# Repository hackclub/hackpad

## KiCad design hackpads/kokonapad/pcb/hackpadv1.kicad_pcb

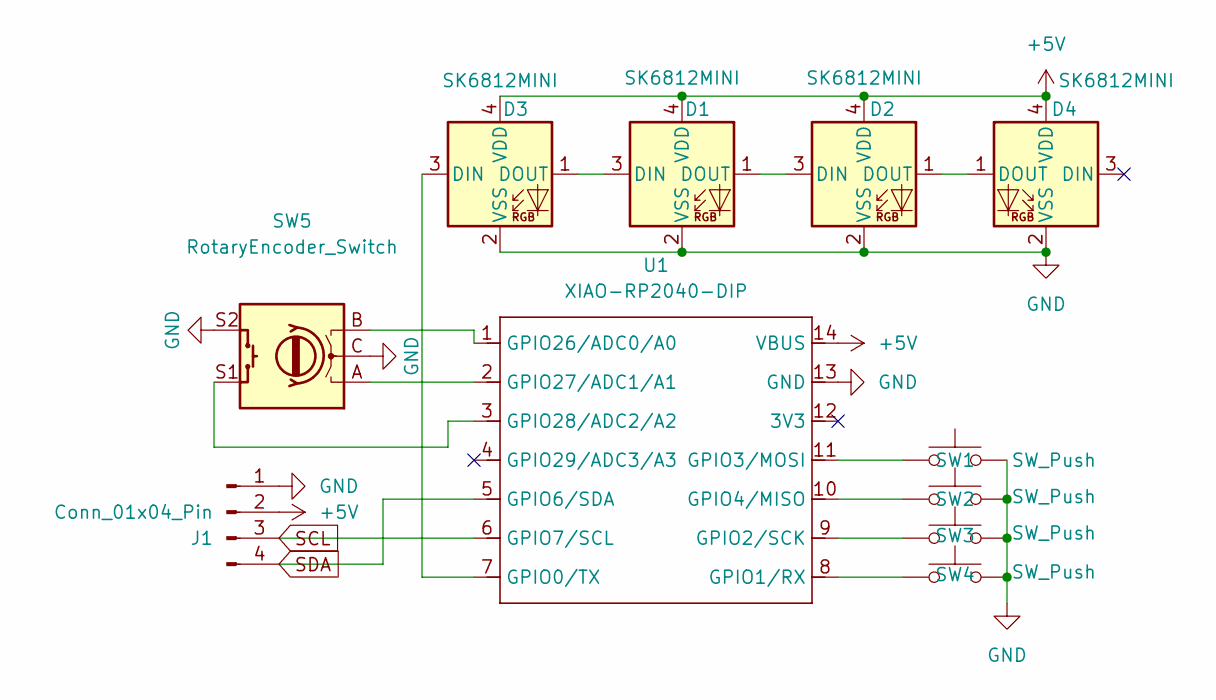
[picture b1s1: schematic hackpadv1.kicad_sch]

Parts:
D1, D2, D3, D4: SK6812MINI; LED_SK6812MINI_PLCC4_3.5x3.5mm_P1.75mm
J1: Conn_01x04_Pin; SSD1306-0.91-OLED-4pin-128x32
SW1, SW2, SW3, SW4: SW_Push; SW_Cherry_MX_1.00u_PCB
SW5: RotaryEncoder_Switch; RotaryEncoder_Alps_EC11E-Switch_Vertical_H20mm_CircularMoun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
U1: XIAO-RP2040-DIP

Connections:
+5V: D1.4 (VDD), D2.4 (VDD), D3.4 (VDD), D4.4 (VDD), J1.2, U1.14 (VBUS)
GND: D1.2 (VSS), D2.2 (VSS), D3.2 (VSS), D4.2 (VSS), J1.1, SW1.2, SW2.2, SW3.2, SW4.2, SW5.C, SW5.S2, U1.13 (GND)
unnamed: D1.3 (DIN), D3.1 (DOUT)
unnamed: D1.1 (DOUT), D2.3 (DIN)
unnamed: D2.1 (DOUT), D4.1 (DOUT)
unnamed: D3.3 (DIN), U1.7 (GPIO0/TX)
unnamed: SW4.1, U1.8 (GPIO1/RX)
unnamed: SW3.1, U1.9 (GPIO2/SCK)
unnamed: SW1.1, U1.11 (GPIO3/MOSI)
unnamed: SW2.1, U1.10 (GPIO4/MISO)
unnamed: SW5.B, U1.1 (GPIO26/ADC0/A0)
unnamed: SW5.A, U1.2 (GPIO27/ADC1/A1)
unnamed: SW5.S1, U1.3 (GPIO28/ADC2/A2)
SCL: J1.3, U1.6 (GPIO7/SCL)
SDA: J1.4, U1.5 (GPIO6/SDA)

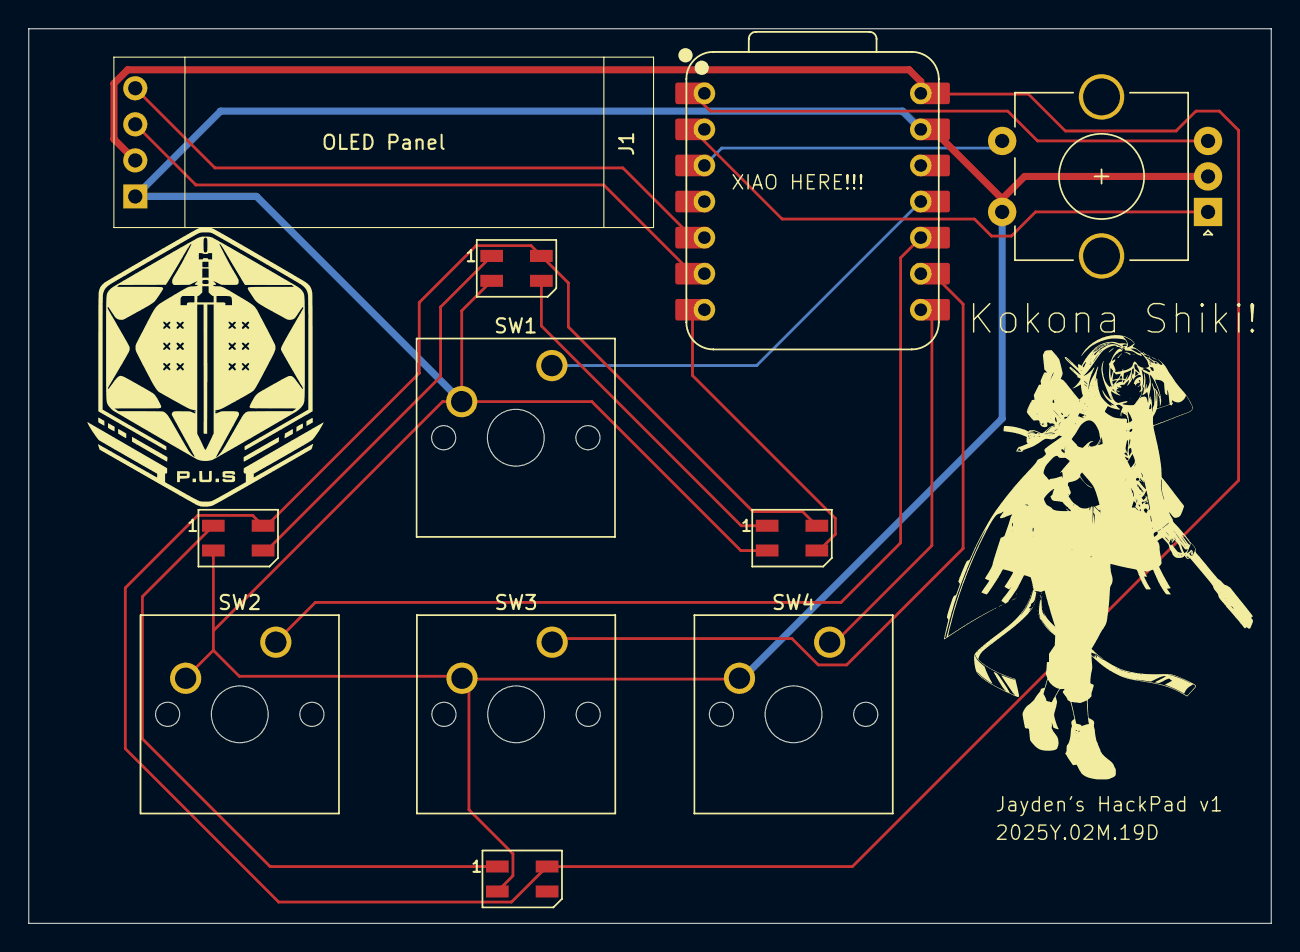
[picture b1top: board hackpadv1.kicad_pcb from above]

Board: 2 copper layers, 87.5 x 63.0 mm, 11 parts (0 on the bottom side), 15 nets.

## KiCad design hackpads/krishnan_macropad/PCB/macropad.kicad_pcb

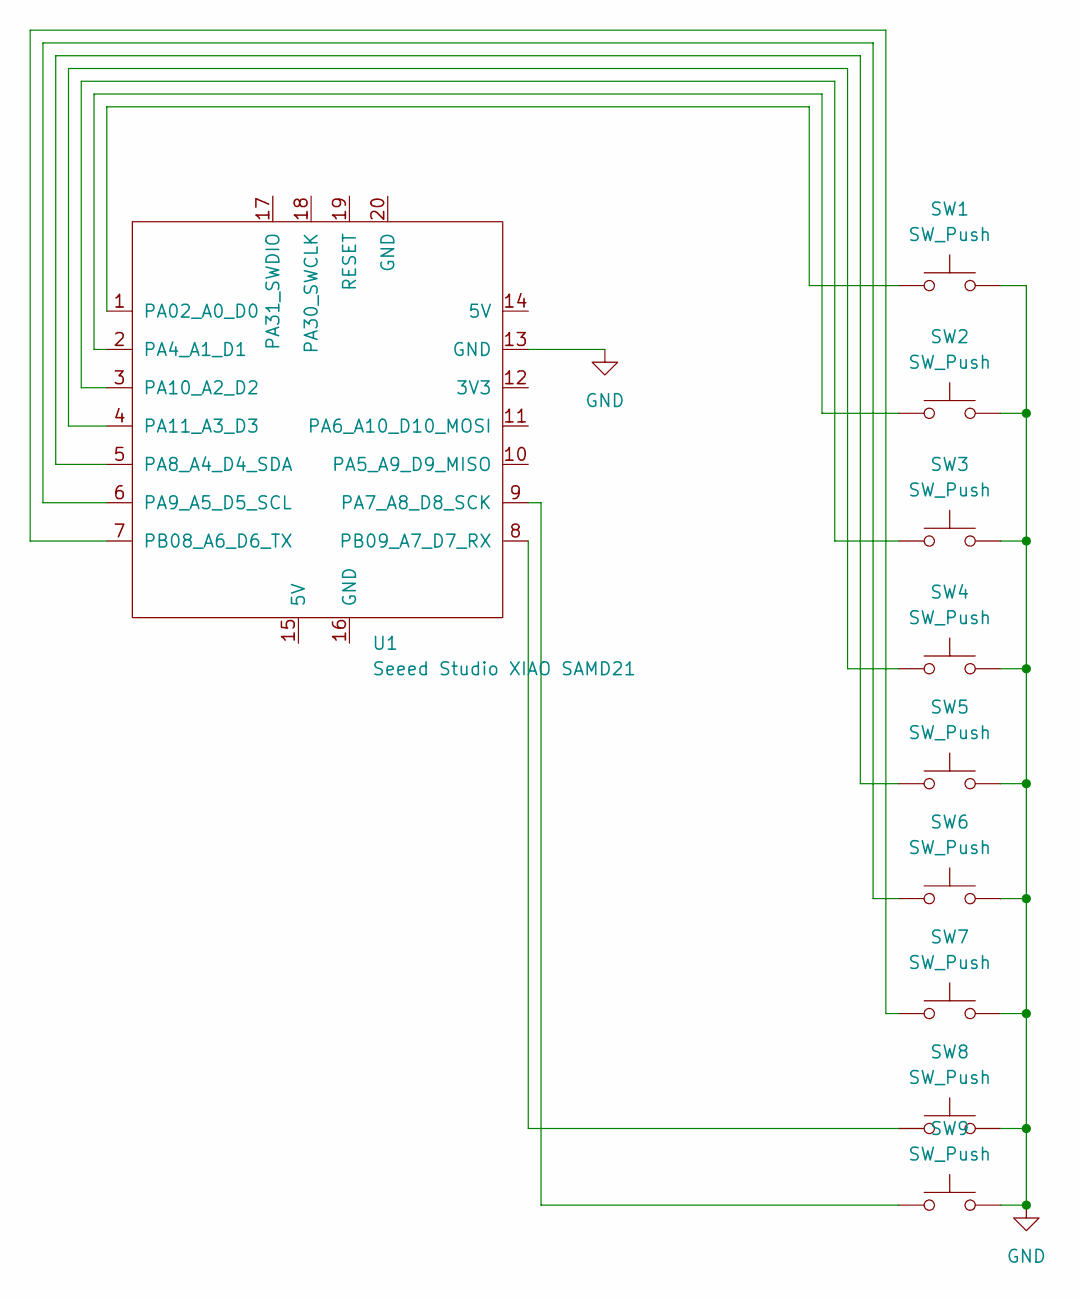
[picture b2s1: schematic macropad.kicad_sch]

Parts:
SW1, SW2, SW3, SW4, SW5, SW6, SW7, SW8, SW9: SW_Push; SW_Cherry_MX_1.00u_PCB
U1: Seeed Studio XIAO SAMD21; XIAO-RP2040-DIP

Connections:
GND: SW1.2, SW2.2, SW3.2, SW4.2, SW5.2, SW6.2, SW7.2, SW8.2, SW9.2, U1.13 (GND)
unnamed: SW1.1, U1.1 (PA02_A0_D0)
unnamed: SW2.1, U1.2 (PA4_A1_D1)
unnamed: SW9.1, U1.9 (PA7_A8_D8_SCK)
unnamed: SW5.1, U1.5 (PA8_A4_D4_SDA)
unnamed: SW6.1, U1.6 (PA9_A5_D5_SCL)
unnamed: SW3.1, U1.3 (PA10_A2_D2)
unnamed: SW4.1, U1.4 (PA11_A3_D3)
unnamed: SW7.1, U1.7 (PB08_A6_D6_TX)
unnamed: SW8.1, U1.8 (PB09_A7_D7_RX)

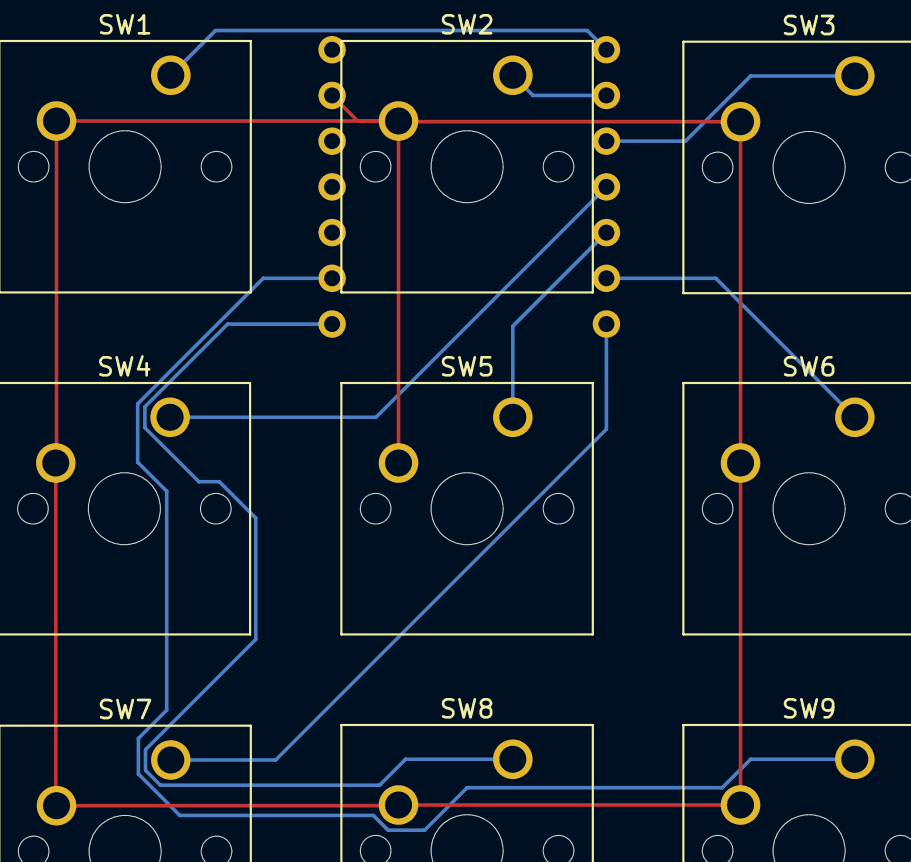
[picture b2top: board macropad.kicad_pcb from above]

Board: 2 copper layers, 10 parts (1 on the bottom side), 10 nets.

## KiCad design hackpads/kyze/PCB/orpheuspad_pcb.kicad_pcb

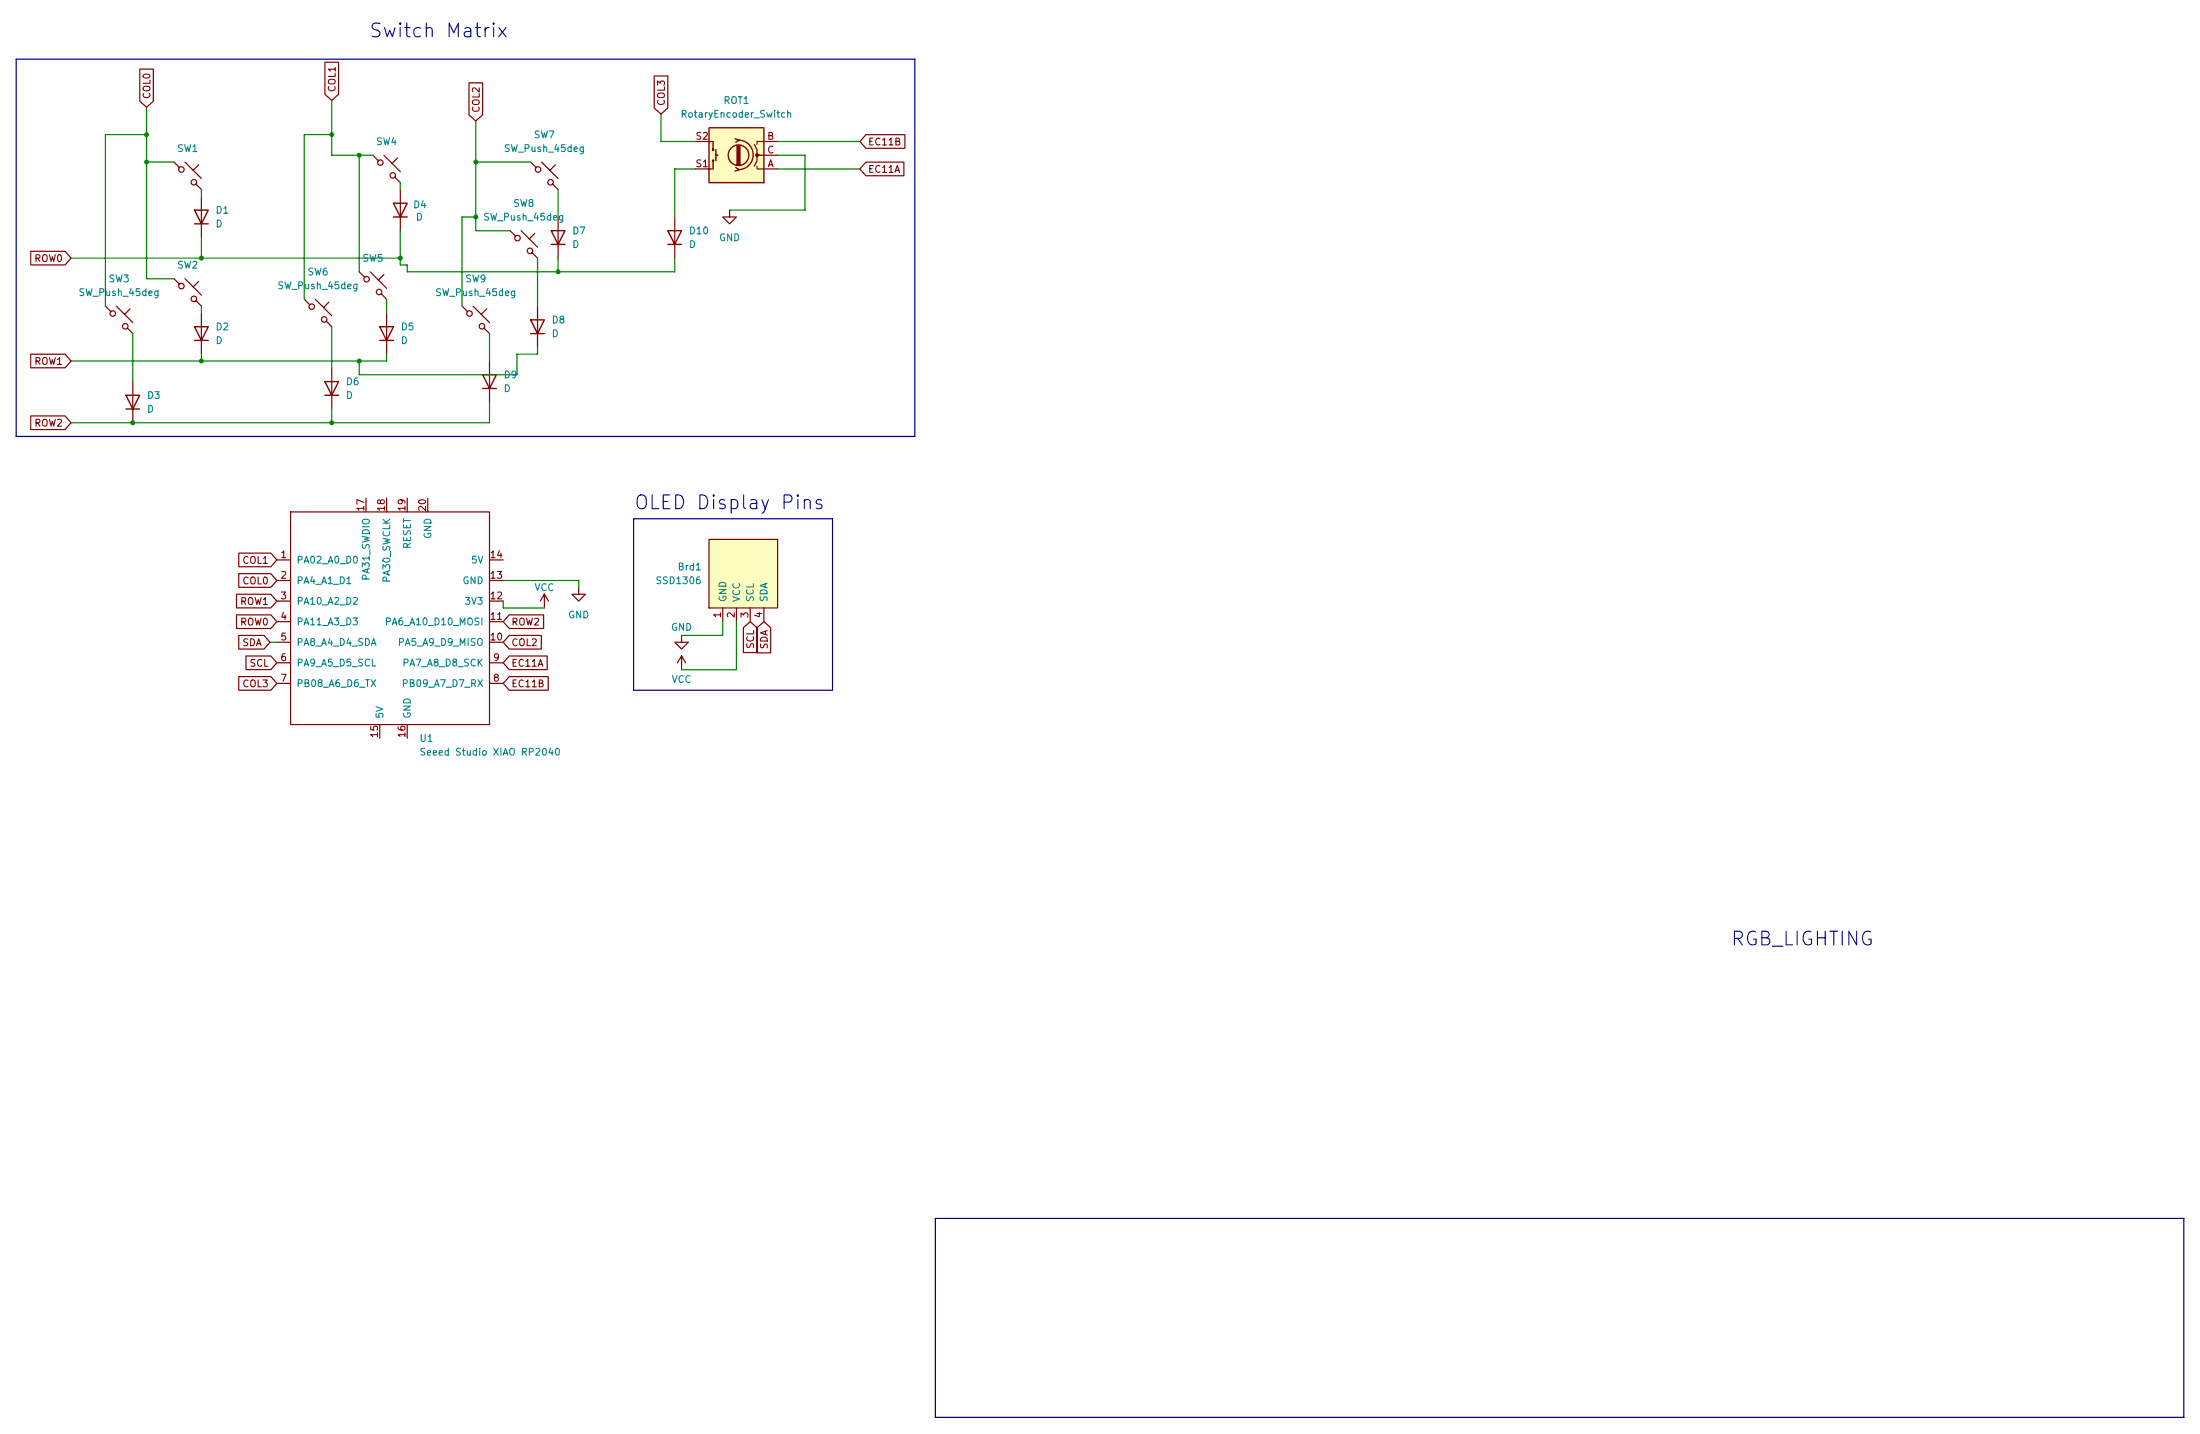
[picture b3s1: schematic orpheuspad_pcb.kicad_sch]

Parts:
Brd1: SSD1306; 128x64OLED
D1, D2, D3, D4, D5, D6, D7, D8, D9, D10: D; D_DO-35_SOD27_P7.62mm_Horizontal
ROT1: RotaryEncoder_Switch; RotaryEncoder_Alps_EC11E-Switch_Vertical_H20mm
SW1, SW2, SW3, SW4, SW5, SW6, SW7, SW8, SW9: SW_Push_45deg; MX-Solderable-1U
U1: Seeed Studio XIAO RP2040; XIAO-Generic-Hybrid-14P-2.54-21X17.8MM

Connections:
COL0: SW1.1, SW2.1, SW3.1, U1.2 (PA4_A1_D1)
COL1: SW4.1, SW5.1, SW6.1, U1.1 (PA02_A0_D0)
COL2: SW7.1, SW8.1, SW9.1, U1.10 (PA5_A9_D9_MISO)
COL3: ROT1.S2, U1.7 (PB08_A6_D6_TX)
EC11A: ROT1.A, U1.9 (PA7_A8_D8_SCK)
EC11B: ROT1.B, U1.8 (PB09_A7_D7_RX)
GND: Brd1.1 (GND), ROT1.C, U1.13 (GND)
unnamed: D1.2 (A), SW1.2
unnamed: D2.2 (A), SW2.2
unnamed: D3.2 (A), SW3.2
unnamed: D4.2 (A), SW4.2
unnamed: D5.2 (A), SW5.2
unnamed: D6.2 (A), SW6.2
unnamed: D7.2 (A), SW7.2
unnamed: D8.2 (A), SW8.2
unnamed: D9.2 (A), SW9.2
unnamed: D10.2 (A), ROT1.S1
ROW0: D1.1 (K), D4.1 (K), D7.1 (K), D10.1 (K), U1.4 (PA11_A3_D3)
ROW1: D2.1 (K), D5.1 (K), D8.1 (K), U1.3 (PA10_A2_D2)
ROW2: D3.1 (K), D6.1 (K), D9.1 (K), U1.11 (PA6_A10_D10_MOSI)
SCL: Brd1.3 (SCL), U1.6 (PA9_A5_D5_SCL)
SDA: Brd1.4 (SDA), U1.5 (PA8_A4_D4_SDA)
VCC: Brd1.2 (VCC), U1.12 (3V3)

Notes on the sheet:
RGB_LIGHTING
Switch Matrix
OLED Display Pins

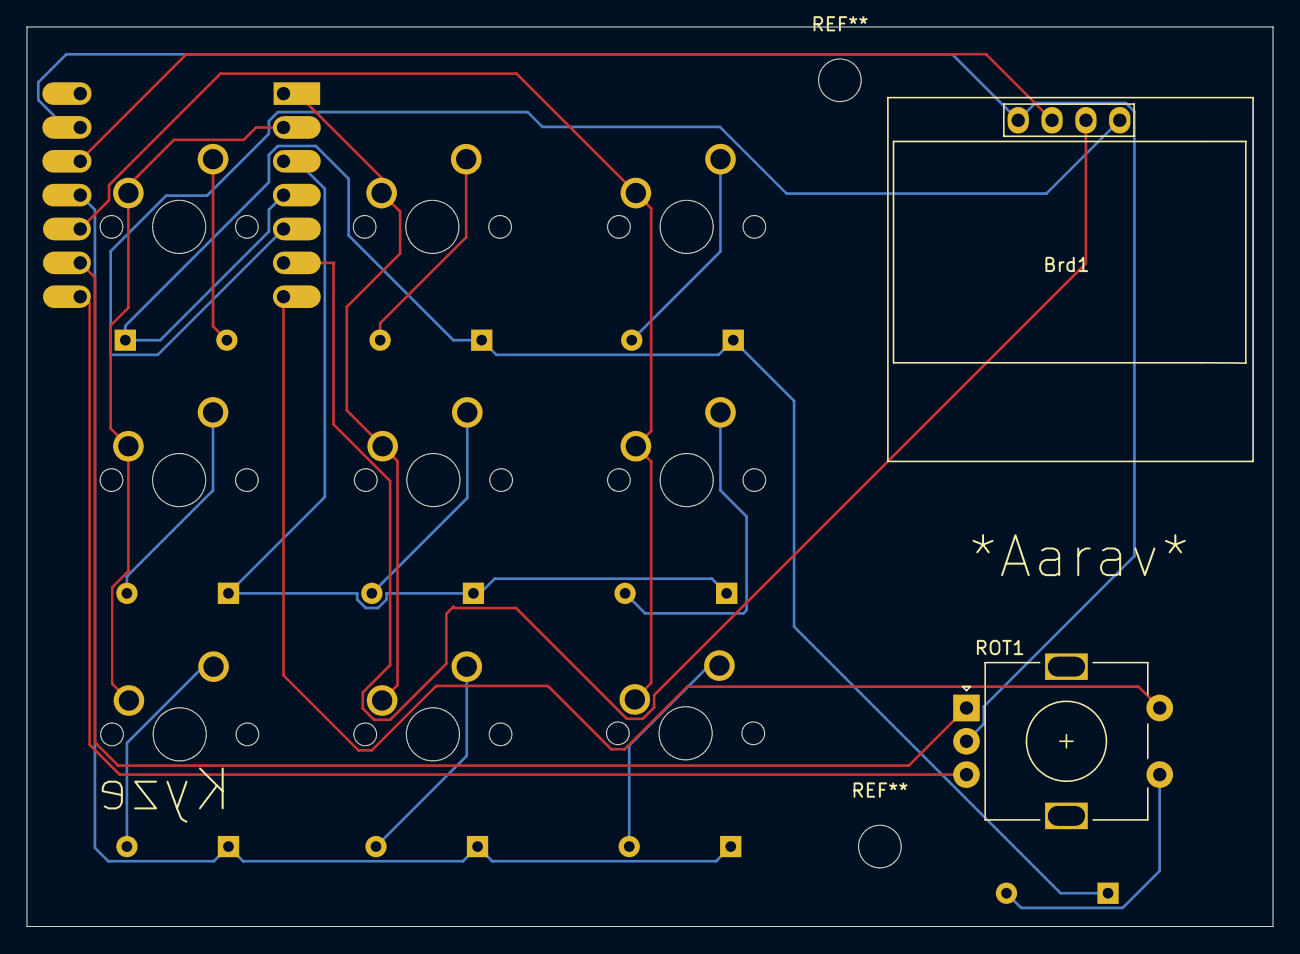
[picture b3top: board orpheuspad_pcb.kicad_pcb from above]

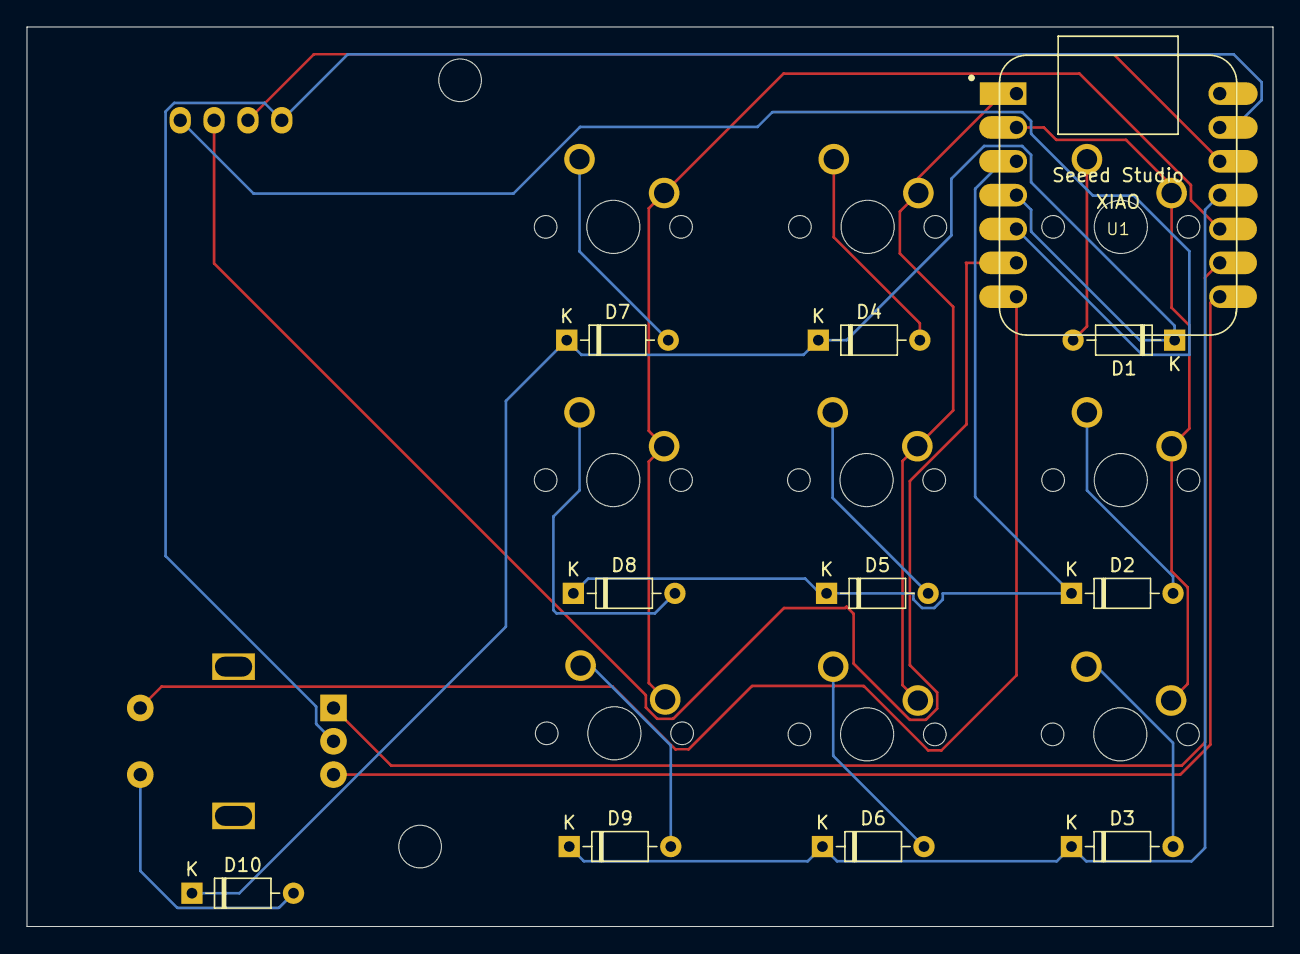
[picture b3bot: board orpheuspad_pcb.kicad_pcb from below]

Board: 2 copper layers, 93.5 x 67.5 mm, 22 parts (11 on the bottom side), 23 nets.

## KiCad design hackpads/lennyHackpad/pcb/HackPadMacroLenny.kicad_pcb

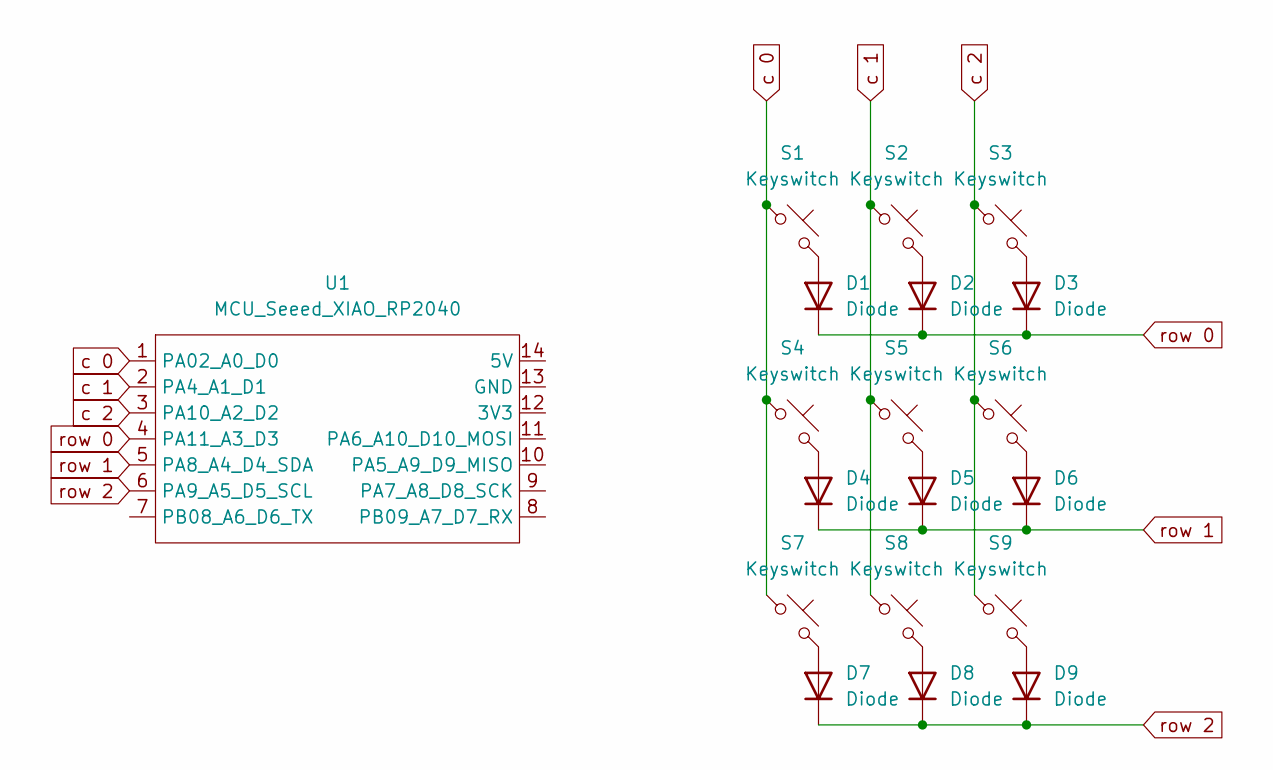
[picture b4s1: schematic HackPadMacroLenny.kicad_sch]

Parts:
D1, D2, D3, D4, D5, D6, D7, D8, D9: Diode; Diode_DO-35
S1, S2, S3, S4, S5, S6, S7, S8, S9: Keyswitch; MX_PCB_1.00u
U1: MCU_Seeed_XIAO_RP2040; Seeed_XIAO_RP2040

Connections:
unnamed: D1.2 (A), S1.2
unnamed: D2.2 (A), S2.2
unnamed: D3.2 (A), S3.2
unnamed: D4.2 (A), S4.2
unnamed: D5.2 (A), S5.2
unnamed: D6.2 (A), S6.2
unnamed: D7.2 (A), S7.2
unnamed: D8.2 (A), S8.2
unnamed: D9.2 (A), S9.2
c 0: S1.1, S4.1, S7.1, U1.1 (PA02_A0_D0)
c 1: S2.1, S5.1, S8.1, U1.2 (PA4_A1_D1)
c 2: S3.1, S6.1, S9.1, U1.3 (PA10_A2_D2)
row 0: D1.1 (K), D2.1 (K), D3.1 (K), U1.4 (PA11_A3_D3)
row 1: D4.1 (K), D5.1 (K), D6.1 (K), U1.5 (PA8_A4_D4_SDA)
row 2: D7.1 (K), D8.1 (K), D9.1 (K), U1.6 (PA9_A5_D5_SCL)

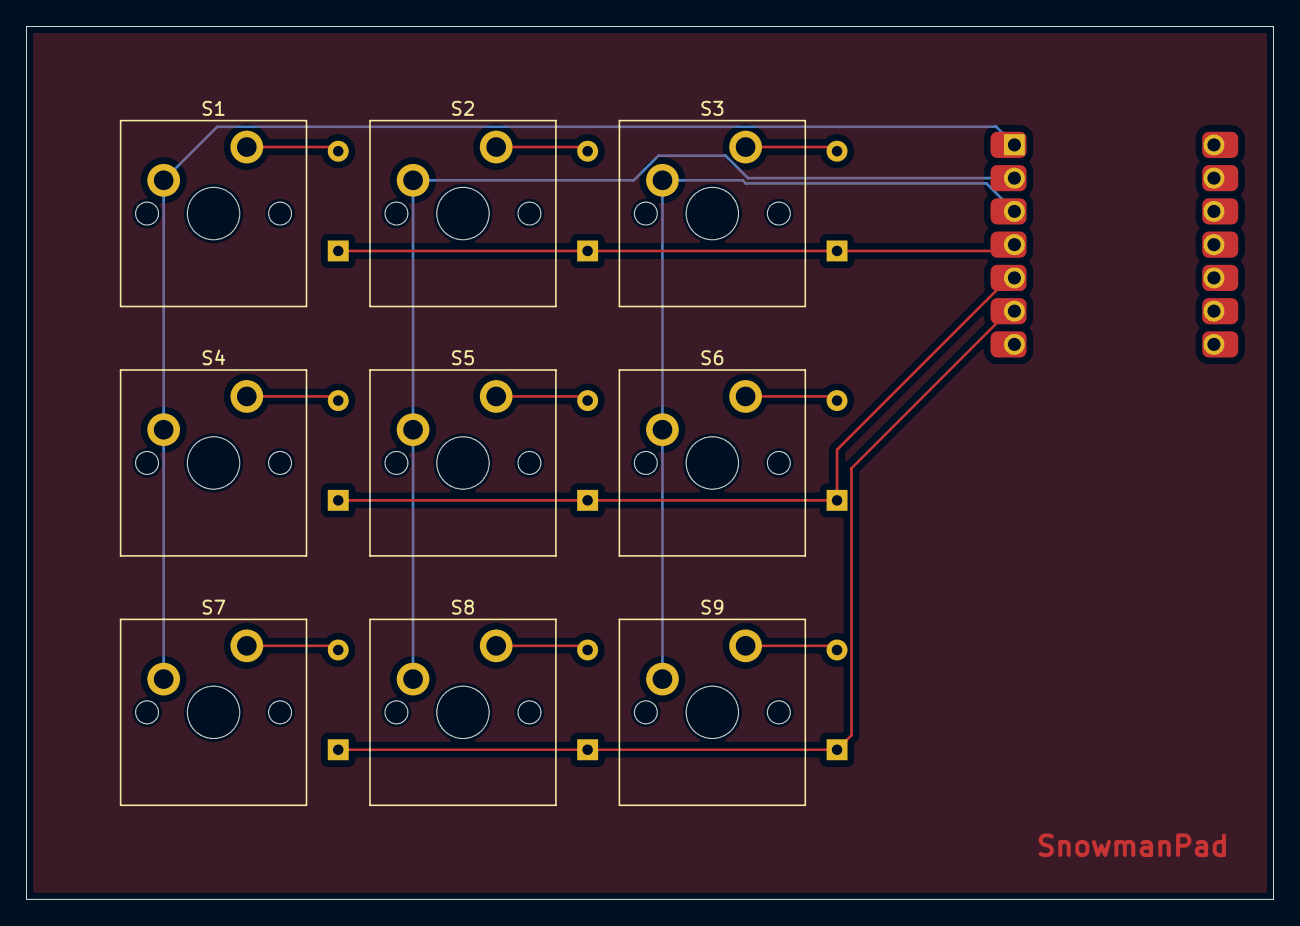
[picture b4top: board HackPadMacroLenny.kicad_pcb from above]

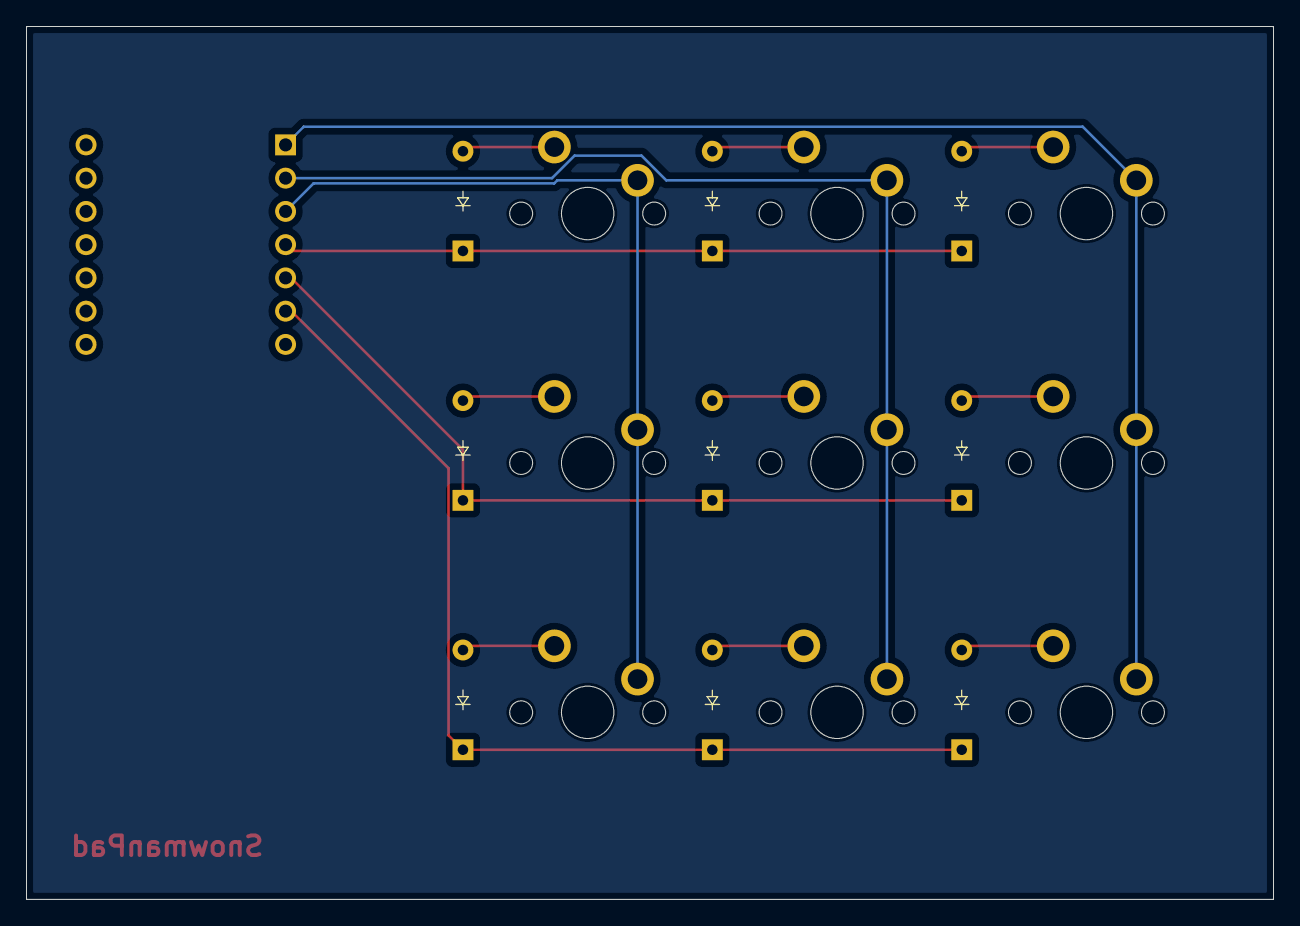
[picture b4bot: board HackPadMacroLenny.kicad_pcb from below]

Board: 2 copper layers, 95.2 x 66.7 mm, 19 parts (9 on the bottom side), 15 nets.

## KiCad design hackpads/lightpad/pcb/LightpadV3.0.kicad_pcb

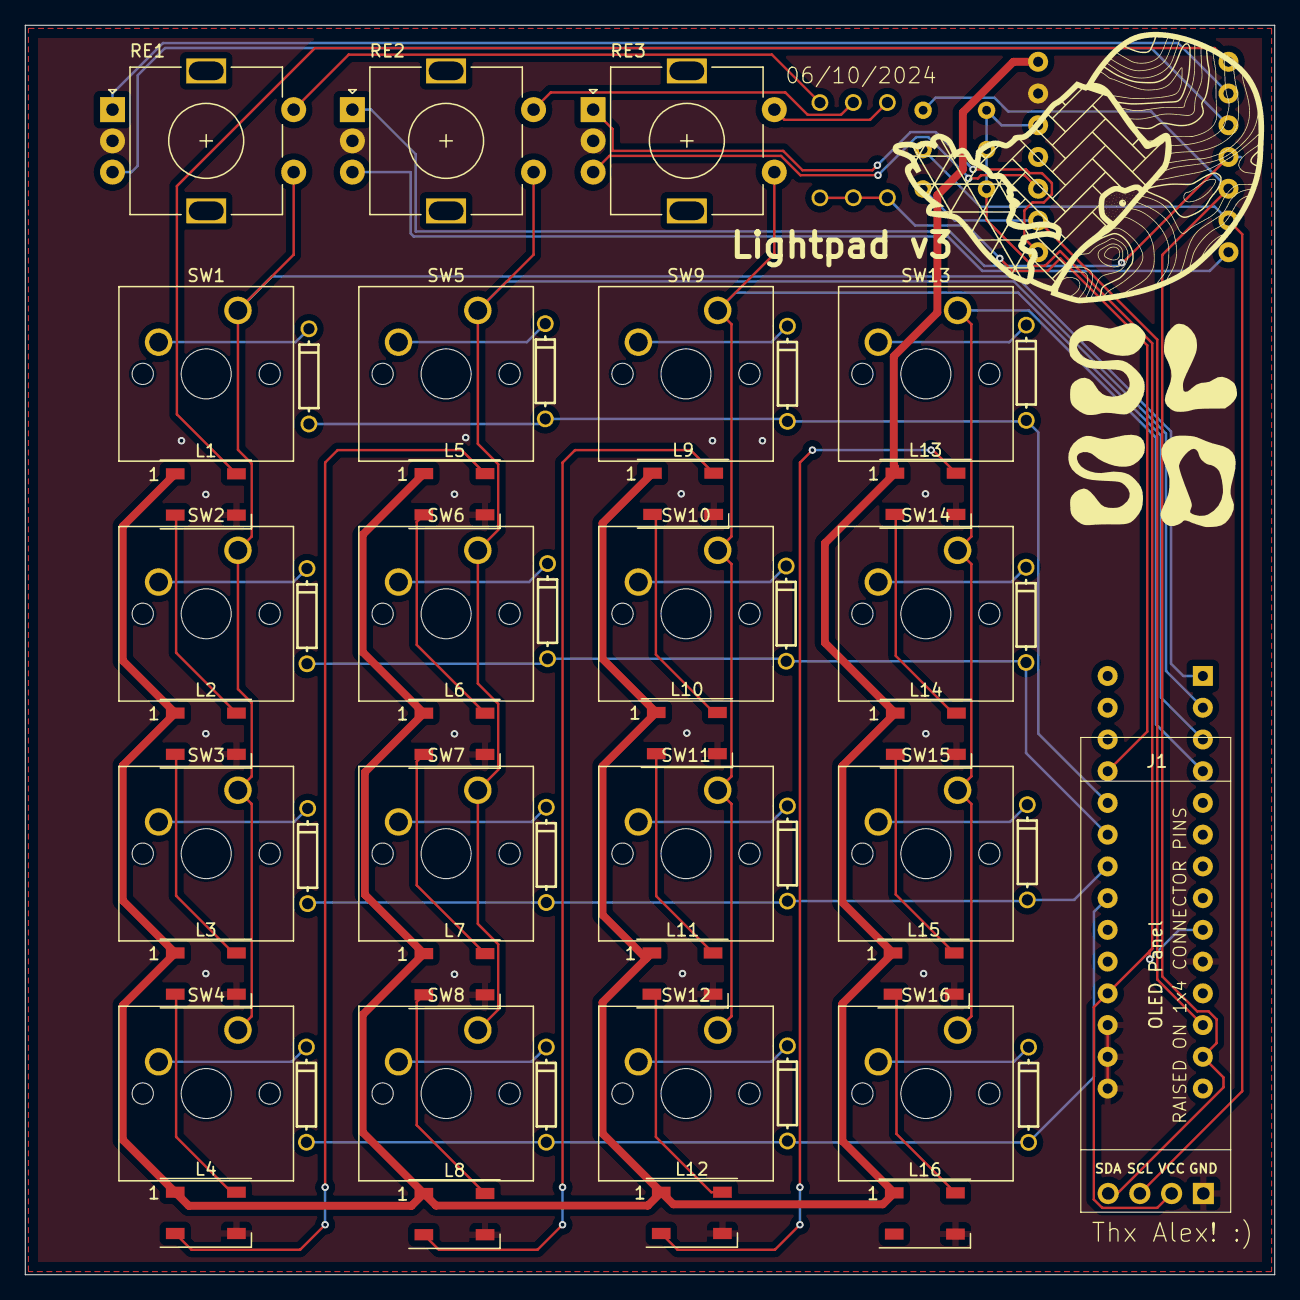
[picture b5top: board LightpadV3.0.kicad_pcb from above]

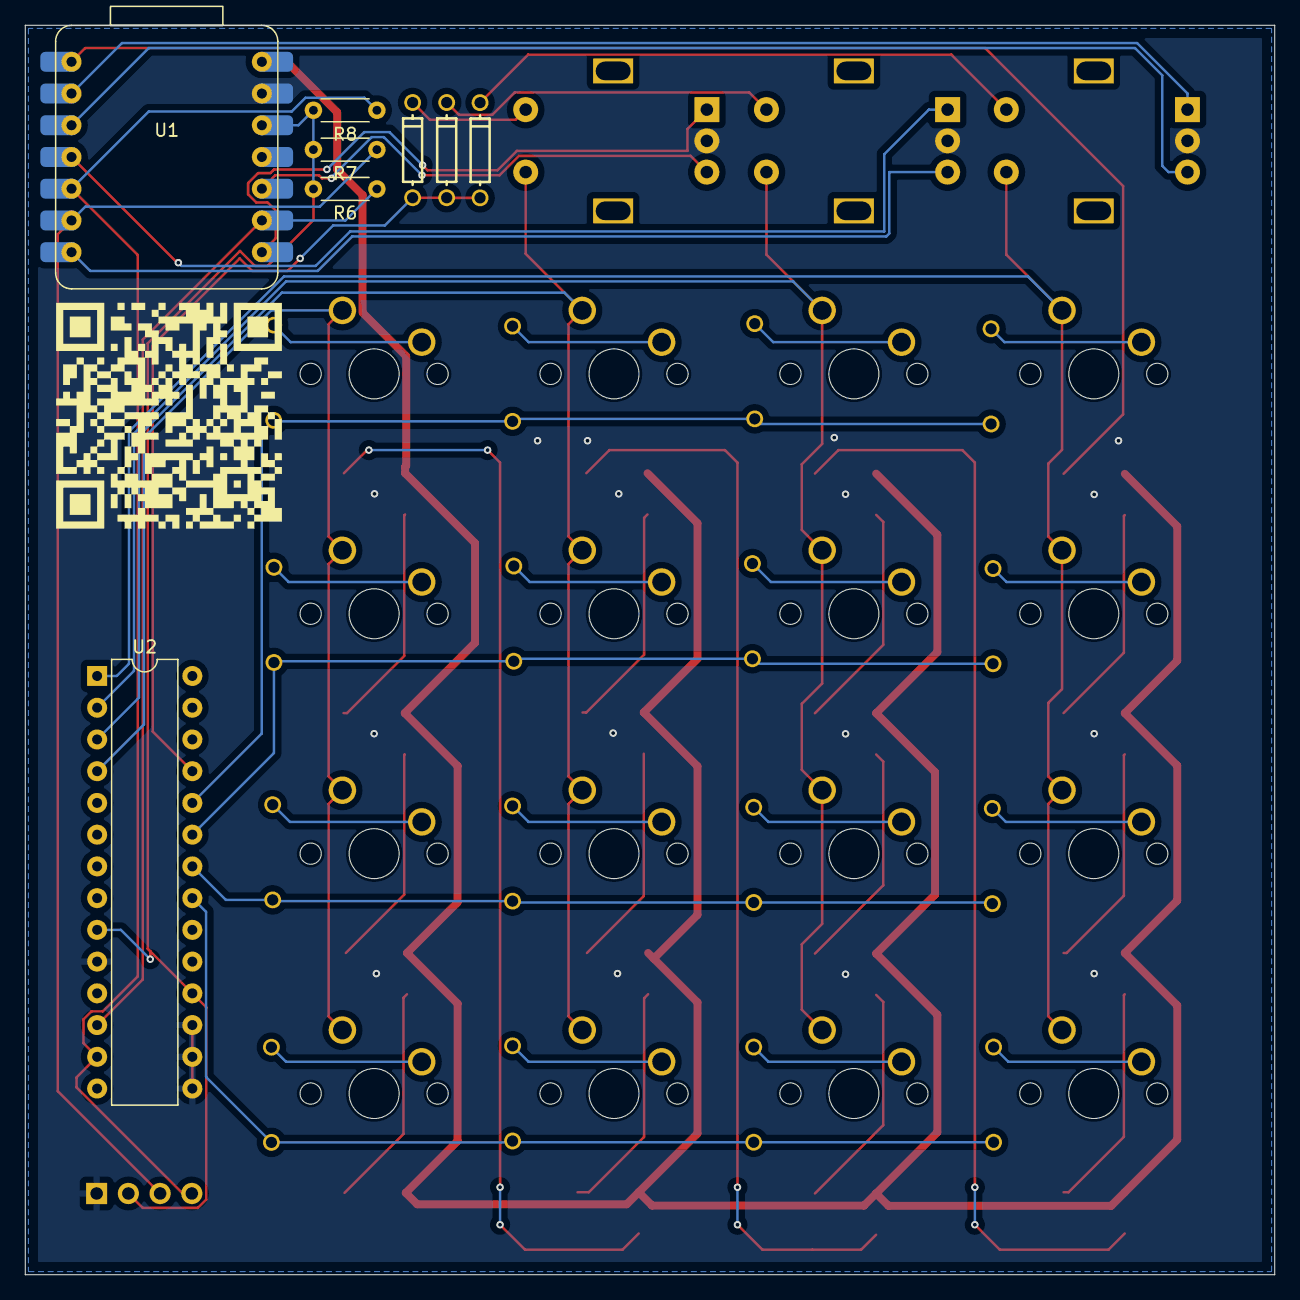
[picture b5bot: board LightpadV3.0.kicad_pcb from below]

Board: 2 copper layers, 100.0 x 100.0 mm, 60 parts (8 on the bottom side), 56 nets.

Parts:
D1, D2, D3, D4, D5, D6, D7, D8, D9, D10, D11, D12, D13, D14, D15, D16, D17, D18, D19: D; DIODE-1N4148
J1: 0.91" OLED Display; SSD1306-0.91-OLED-4pin-128x32
L1, L2, L3, L4, L5, L6, L7, L8, L9, L10, L11, L12, L13, L14, L15, L16: WS2812B; LED_WS2812B_PLCC4_5.0x5.0mm_P3.2mm
R6, R7, R8: 4.7K; R_Axial_DIN0204_L3.6mm_D1.6mm_P5.08mm_Horizontal
RE1, RE2, RE3: E11 Rotary; ec11with3dmodel
SW1, SW2, SW3, SW4, SW5, SW6, SW7, SW8, SW9, SW10, SW11, SW12, SW13, SW14, SW15, SW16: Cherry MX Switch; mxswitchwithmodel
U1: Seeed Studio RP2040; XIAO-RP2040
U2: MCP23017_SP; DIP-28_W7.62mm

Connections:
+3V3: J1.2, R6.2, R7.2, R8.2, U1.12 (3V3), U2.9 (VDD), U2.18 (~RESET)
+5V: L1.1 (VDD), L2.1 (VDD), L3.1 (VDD), L4.1 (VDD), L5.1 (VDD), L6.1 (VDD), L7.1 (VDD), L8.1 (VDD), L9.1 (VDD), L10.1 (VDD), L11.1 (VDD), L12.1 (VDD), L13.1 (VDD), L14.1 (VDD), L15.1 (VDD), L16.1 (VDD), U1.14 (5V)
C1: RE1.S1, SW1.1, SW2.1, SW3.1, SW4.1, U2.1 (GPB0)
C2: RE2.S1, SW5.1, SW6.1, SW7.1, SW8.1, U2.2 (GPB1)
C3: RE3.S1, SW9.1, SW10.1, SW11.1, SW12.1, U2.3 (GPB2)
C4: SW13.1, SW14.1, SW15.1, SW16.1, U2.4 (GPB3)
E1A: RE1.A, U1.2 (PA4_A1_D1)
E1B: RE1.B, U1.3 (PA10_A2_D2)
E2A: RE2.A, U1.4 (PA11_A3_D3)
E2B: RE2.B, U1.7 (PB08_A6_D6_TX)
E3A: RE3.A, U1.8 (PB09_A7_D7_RX)
E3B: RE3.B, U1.10 (PA5_A9_D9_MISO)
GND: J1.1, L1.3 (VSS), L2.3 (VSS), L3.3 (VSS), L4.3 (VSS), L5.3 (VSS), L6.3 (VSS), L7.3 (VSS), L8.3 (VSS), L9.3 (VSS), L10.3 (VSS), L11.3 (VSS), L12.3 (VSS), L13.3 (VSS), L14.3 (VSS), L15.3 (VSS), L16.3 (VSS), RE1.C, RE2.C, RE3.C, U1.13 (GND), U2.10 (VSS), U2.15 (A0), U2.16 (A1), U2.17 (A2)
N1: L1.4 (DIN), U1.1 (PA02_A0_D0)
unnamed: D1.2 (A), SW1.2
unnamed: D2.2 (A), SW2.2
unnamed: D3.2 (A), SW3.2
unnamed: D4.2 (A), SW4.2
unnamed: D5.2 (A), SW5.2
unnamed: D6.2 (A), SW6.2
unnamed: D7.2 (A), SW7.2
unnamed: D8.2 (A), SW8.2
unnamed: D9.2 (A), SW9.2
unnamed: D10.2 (A), SW10.2
unnamed: D11.2 (A), SW11.2
unnamed: D12.2 (A), SW12.2
unnamed: D13.2 (A), SW13.2
unnamed: D14.2 (A), SW14.2
unnamed: D15.2 (A), SW15.2
unnamed: D16.2 (A), SW16.2
unnamed: D17.2 (A), RE1.S2
unnamed: D18.2 (A), RE2.S2
unnamed: D19.2 (A), RE3.S2
unnamed: L1.2 (DOUT), L2.4 (DIN)
unnamed: L2.2 (DOUT), L3.4 (DIN)
unnamed: L3.2 (DOUT), L4.4 (DIN)
unnamed: L4.2 (DOUT), L5.4 (DIN)
unnamed: L5.2 (DOUT), L6.4 (DIN)
unnamed: L6.2 (DOUT), L7.4 (DIN)
unnamed: L7.2 (DOUT), L8.4 (DIN)
unnamed: L8.2 (DOUT), L9.4 (DIN)
unnamed: L9.2 (DOUT), L10.4 (DIN)
unnamed: L10.2 (DOUT), L11.4 (DIN)
unnamed: L11.2 (DOUT), L12.4 (DIN)
unnamed: L12.2 (DOUT), L13.4 (DIN)
unnamed: L13.2 (DOUT), L14.4 (DIN)
unnamed: L14.2 (DOUT), L15.4 (DIN)
unnamed: L15.2 (DOUT), L16.4 (DIN)
R1: D1.1 (K), D5.1 (K), D9.1 (K), D13.1 (K), U2.24 (GPA3)
R2: D2.1 (K), D6.1 (K), D10.1 (K), D14.1 (K), U2.23 (GPA2)
R3: D3.1 (K), D7.1 (K), D11.1 (K), D15.1 (K), U2.22 (GPA1)
R4: D4.1 (K), D8.1 (K), D12.1 (K), D16.1 (K), U2.21 (GPA0)
R5: D17.1 (K), D18.1 (K), D19.1 (K), U2.25 (GPA4)
SCK: R6.1, U1.9 (PA7_A8_D8_SCK), U2.12 (SCK)
SCL: J1.3, R7.1, U1.6 (PA9_A5_D5_SCL)
SDA: J1.4, R8.1, U1.5 (PA8_A4_D4_SDA), U2.13 (SDA)
